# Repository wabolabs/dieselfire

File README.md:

# DieselFire

> **⚠ ALPHA QUALITY — NOT TESTED ON HARDWARE**
>
> This project is in early development. The firmware has **not** been tested on
> physical ESP32-S3 hardware. All protocol simulation and UI development has
> been done via the **PC simulator**. There are likely bugs, edge cases, and
> incomplete drivers. Use at your own risk. Hardware bringup is in progress.

A modernized open-source controller for generic Chinese diesel heaters, forked from [Afterburner](https://gitlab.com/mrjones.id.au/bluetoothheater) by Ray Jones.

## Overview

DieselFire is a complete redesign of the Afterburner project, updated with modern hardware while preserving the core functionality that made Afterburner popular:

- **Diesel heater control** via the "blue wire" half-duplex serial protocol (25000 baud)
- **WiFi connectivity** for web interface, MQTT, and OTA updates
- **Bluetooth Low Energy** for mobile app control
- **Environmental monitoring** with temperature, humidity, pressure, and CO detection
- **Color touchscreen UI** with LVGL graphics
- **Programmable timers** (14 channels)
- **Fuel gauge** and hour meter
- **Smart error detection**

## Online Simulator

Try the DieselFire UI in your browser without any hardware:
**[dieselfire.wabo.cc](https://dieselfire.wabo.cc)**

Runs as a WebAssembly build of the native PC simulator. Includes the full
touchscreen interface, Blue Wire protocol simulation, and a diesel heater
emulator for testing all states and fault conditions.

## Hardware

| Component | Specification |
|---|---|
| **MCU** | ESP32-S3-WROOM-1-N8R8 (8MB flash, 8MB PSRAM) |
| **Display** | 2.8" 320×240 ILI9341 TFT with capacitive touch (GT911) |
| **Ambient Sensor** | BME280 (temperature, humidity, pressure/altitude) |
| **CO Sensor** | MQ-7 carbon monoxide (external module) |
| **RTC** | DS3231 with CR2032 battery backup |
| **External Temp** | DS18B20 waterproof probe (optional) |
| **Power** | 12V DC input (heater system voltage) |
| **Connectivity** | USB-C (programming/debug), WiFi, BLE 5 |
| **Expansion** | 2× 2×10 GPIO headers |

## License

DieselFire is released under the **GNU General Public License v3.0**.

This project is a **fork** of [Afterburner](https://gitlab.com/mrjones.id.au/bluetoothheater) by Ray Jones (Copyright 2018-2020). The original Afterburner code was used as the foundation and has been substantially modified and modernized. All original Afterburner code remains under GPLv3 as per the original license.

See [LICENSE](LICENSE) for the full license text.

## Quick Start

1. **Hardware**: Order PCB from JLCPCB/PCBWay using Gerber files in `gerber/`
2. **Firmware**: Install PlatformIO, then run `pio run` to build
3. **Flash**: Connect via USB-C and run `pio run --target upload`
4. **Configure**: Connect to the AP "DieselFire" (password: thereisnospoon) or connect to existing WiFi

## Project Structure

```
DieselFire/
├── boards/                  # PlatformIO board definitions
├── docs/
│   ├── design/              # Design documents and specifications
│   ├── firmware/            # Firmware documentation
│   └── hardware/            # Hardware documentation
├── gerber/                  # PCB fabrication files
├── kicad/
│   ├── schematic/           # KiCad schematic files
│   ├── pcb/                 # KiCad PCB layout files
│   ├── footprints/          # Custom KiCad footprints
│   └── libraries/           # KiCad symbol libraries
├── lib/                     # PlatformIO libraries (vendored)
├── src/
│   ├── cfg/                 # Configuration headers
│   ├── Display/             # LVGL display driver and screens
│   ├── Protocol/            # Blue wire protocol handling
│   ├── RTC/                 # Real-time clock and timers
│   ├── Utility/             # Utility classes (sensors, storage, etc.)
│   ├── WiFi/                # WiFi, web server, OTA
│   ├── Bluetooth/           # BLE implementation
│   └── OLED/                # Legacy OLED code (to be removed)
├── platformio.ini           # PlatformIO project configuration
├── README.md
└── LICENSE
```

## Features

### Heater Control
- Power on/off commands
- Temperature setpoint adjustment
- Fuel mixture tuning
- Pump priming
- Thermostat mode (cyclic, stop/start, linear)
- Frost protection mode
- Humidity-based control
- OEM controller co-existence mode

### Connectivity
- **WiFi**: STA mode (connect to existing network) or AP mode (captive portal)
- **BLE 5**: Bluetooth Low Energy for mobile app control
- **MQTT**: Publish heater status and receive commands
- **Web Server**: HTTPS web interface with WebSocket JSON streaming
- **OTA**: Over-the-air firmware updates

### Sensors
- **BME280**: Ambient temperature, humidity, pressure (altitude)
- **MQ-7**: Carbon monoxide detection (external module)
- **DS18B20**: External waterproof temperature probe (optional)
- **SCD41**: CO2 sensing (optional, not on default board)

### User Interface
- **2.8" Color Touchscreen**: 320×240 ILI9341 with capacitive touch
- **LVGL Graphics**: Hardware-accelerated UI with PSRAM buffer
- **Menu System**: Hierarchical menus for all settings
- **Timer Chart**: Visual overview of 14 programmable timers
- **Status Display**: Real-time heater status, sensor readings, alerts

### Safety
- **CO Detection**: MQ-7 sensor with alarm LED
- **Low Voltage Cutout**: Auto-shutdown when battery voltage is too low
- **Error Detection**: Smart monitoring of heater state transitions
- **Watchdog**: Hardware and software watchdog for reliability

## Pinout

### ESP32-S3 GPIO Mapping

| Peripheral | GPIO | Interface | Notes |
|---|---|---|---|
| **Native USB** | IO19 (DP) / IO20 (DN) | USB 1.1 | USB-C, programming + debug |
| **SPI Display** | IO18 (MOSI) / IO17 (SCK) / IO16 (MISO) | SPI (HSPI) | ILI9341, 320×240 |
| **Display CS** | IO15 | GPIO | TFT chip select |
| **Display DC** | IO14 | GPIO | TFT data/command |
| **Display RST** | IO13 | GPIO | TFT reset |
| **Display BL** | IO12 | GPIO/PWM | TFT backlight |
| **Touch I2C** | IO21 (SDA) / IO10 (SCL) | I2C (GPIO) | GT911 capacitive touch |
| **Touch INT** | IO9 | GPIO | Touch interrupt |
| **Touch RST** | IO8 | GPIO | Touch reset |
| **Blue Wire UART** | IO43 (TX) / IO44 (RX) | UART0 @ 25kbps | Heater communication |
| **Tx Gate** | IO47 | GPIO | 74LCX125 control |
| **BME280 I2C** | IO21 (SDA) / IO22 (SCL) | I2C (VSPI) | Temp/RH/Pressure |
| **DS3231 I2C** | IO21 (SDA) / IO22 (SCL) | I2C (VSPI) | RTC |
| **DS18B20** | IO45 | OneWire | External temp probe |
| **MQ-7 AOUT** | IO4 | ADC1 (12-bit) | CO analog reading |
| **MQ-7 DOUT** | IO5 | GPIO input | CO digital alert |
| **Status LED** | IO48 | GPIO | Green, active-low |
| **CO Alarm LED** | IO44 | GPIO | Red, active-low |
| **Power Button** | IO0 | GPIO (input) | With pull-up |
| **Reset Button** | IO5 | GPIO | Standard boot button |

### Expansion Headers

**H1 (2×10):** GPIO33, GPIO34, GPIO35, GPIO36, GPIO37, GPIO38, GPIO39, GPIO40, 3.3V, GND, GND
**H2 (2×10):** GPIO41, GPIO42, GPIO43, GPIO44, GPIO45, GPIO46, GPIO47, GPIO48, 3.3V, GND, GND

### Connectors

| Connector | Type | Purpose |
|---|---|---|
| J1 | USB-C | Programming, debug, power |
| J2 | 2-pin terminal block (3.81mm) | 12V power input |
| J3 | 3-pin JST-XH (2.5mm) | Blue wire to heater |
| J4 | 3-pin JST-XH (2.5mm) | DS18B20 external temp sensor |
| J5 | 4-pin JST-XH (2.5mm) | MQ-7 CO sensor |
| H1, H2 | 2×10 header (2.54mm) | Expansion GPIO |

## Building

### Prerequisites

- [PlatformIO](https://platformio.org/) (latest version)
- ESP32-S3 compatible board (DieselFire PCB)
- USB-C cable

### Build Commands

```bash
# Install PlatformIO
pip install platformio

# Clone the repository
git clone https://github.com/wabolabs/DieselFire.git
cd DieselFire

# Build firmware
pio run

# Upload to board
pio run --target upload

# Monitor serial output
pio device monitor --baud 115200
```

### Board Definition

The DieselFire board is defined in `boards/dieselfire.json`. To use it:

```bash
pio run -e dieselfire
```

## Configuration

### WiFi Setup

On first boot, the device creates an access point:
- **SSID**: DieselFire
- **Password**: thereisnospoon

Connect to this AP and open a browser to `192.168.4.1` to configure WiFi.

### MQTT Setup

Configure MQTT settings in the web interface or via the debug console:
- Server address
- Port (1883 for MQTT, 8883 for MQTT over TLS)
- Client ID
- Username/Password (if required)
- Topic prefix

### Sensor Calibration

**MQ-7 CO Sensor:**
1. Power on the device in clean air (outdoors)
2. Wait 48-72 hours for the sensor to stabilize
3. Use the web interface to run calibration
4. The R0 value is stored in non-volatile memory

**DS18B20 Temperature Probe:**
1. Connect the probe to J4
2. The probe will be auto-detected on boot
3. Set offset in settings if needed

## Hardware Design

### PCB Specifications

- **Size**: 80mm × 60mm
- **Layers**: 2-layer
- **Trace width**: 0.2mm signal, 0.5mm power, 1mm 12V
- **Via size**: 0.3mm hole / 0.6mm pad
- **Clearance**: 0.15mm minimum

### BOM

| Reference | Part | Package | Qty | Est. Cost |
|---|---|---|---|---|
| U1 | ESP32-S3-WROOM-1-N8R8 | QFN-44 module | 1 | ~$4.00 |
| U2 | 2.8" ILI9341 TFT + FPC | FPC connector | 1 | ~$3.50 |
| U3 | GT911 | QFN-24 4×4 | 1 | ~$0.80 |
| U4 | BME280 | QFN-8 2×2 | 1 | ~$1.50 |
| U5 | MQ-7 | JST-XH 4-pin | 1 | ~$2.00 |
| U6 | DS18B20 | JST-XH 3-pin | 1 | ~$1.50 |
| U7 | DS3231 | SOIC-16 | 1 | ~$2.00 |
| U8 | 74LCX125 | SOIC-14 | 1 | ~$0.30 |
| U9×2 | BSS138 | SOT-23 | 2 | ~$0.10 |
| U10 | MP2451 | SOT-23-6 | 1 | ~$0.50 |
| U11 | AP2112 | SOT-89-3 | 1 | ~$0.20 |
| J1 | USB-C-S6 | SMD | 1 | ~$0.30 |
| J2 | Terminal Block 2×3.81 | TB | 1 | ~$0.20 |
| J3-J5 | JST-XH connectors | 2.5mm | 3 | ~$0.50 |
| BAT1 | CR2032 Holder | — | 1 | ~$0.50 |
| H1,H2 | 2×10 Header | 2.54mm | 2 | ~$0.20 |
| D1,D2 | LED 0603 | 0603 | 2 | ~$0.05 |
| SW1,SW2 | Tactile 6×6 | 6×6mm | 2 | ~$0.10 |
| Various | Resistors/Caps | 0402/0603 | ~20 | ~$1.00 |
| **Total BOM** | | | | **~$19.00** |

**PCB fabrication:** ~$5-10 for 5 boards (JLCPCB/PCBWay, 2-layer, 80×60mm)

## Firmware Development

### Architecture

The firmware follows a modular architecture:

```
┌─────────────────────────────────────────────────────────────┐
│                     DieselFire                                │
│                                                              │
│  ┌─────────────┐  ┌──────────────┐  ┌──────────────────┐   │
│  │  Display    │  │   UI Layer   │  │  Settings/Config │   │
│  │  (LVGL)     │  │  (Screens)   │  │  (NVS Storage)   │   │
│  └─────────────┘  └──────────────┘  └──────────────────┘   │
│                                                              │
│  ┌─────────────┐  ┌──────────────┐  ┌──────────────────┐   │
│  │  Protocol   │  │  Blue Wire   │  │  Sensor Layer    │   │
│  │  Handling   │  │  State Machine│ │  (BME280, MQ-7)  │   │
│  └─────────────┘  └──────────────┘  └──────────────────┘   │
│                                                              │
│  ┌─────────────┐  ┌──────────────┐  ┌──────────────────┐   │
│  │  WiFi/HTTP  │  │  BLE/Bluetooth│ │  MQTT/OTA        │   │
│  └─────────────┘  └──────────────┘  └──────────────────┘   │
│                                                              │
│  ┌──────────────────────────────────────────────────────┐   │
│  │                    ESP32-S3 Hardware                  │   │
│  └──────────────────────────────────────────────────────┘   │
└─────────────────────────────────────────────────────────────┘
```

### Key Modules

| Module | Description | Location |
|---|---|---|
| **Display** | LVGL integration, ILI9341 driver, GT911 touch | `src/Display/` |
| **Protocol** | Blue wire protocol, state machine, Tx management | `src/Protocol/` |
| **RTC** | Real-time clock, timers, timer manager | `src/RTC/` |
| **Utility** | Sensors, NV storage, JSON, GPIO helpers | `src/Utility/` |
| **WiFi** | WiFiManager, web server, OTA, MQTT | `src/WiFi/` |
| **Bluetooth** | BLE implementation | `src/Bluetooth/` |
| **OLED** | Legacy OLED screens (to be replaced by LVGL) | `src/OLED/` |

### Development Workflow

1. **Create a feature branch**
   ```bash
   git checkout -b feature/new-screen
   ```

2. **Make changes**
   - Add/modify code in `src/`
   - Update documentation in `docs/`

3. **Build and test**
   ```bash
   pio run
   pio run --target upload
   pio device monitor --baud 115200
   ```

4. **Commit and push**
   ```bash
   git add .
   git commit -m "Add new screen for timer overview"
   git push origin feature/new-screen
   ```

5. **Create a pull request**

## Troubleshooting

### Board Won't Flash

- Check USB-C cable (must be data-capable, not charge-only)
- Hold BOOT button while pressing RESET
- Check COM port in `platformio.ini`

### Display Not Working

- Verify FPC connector is seated correctly
- Check SPI pin connections
- Verify PSRAM is detected (check serial output)

### BME280 Not Detected

- Check I2C address (0x76 or 0x77)
- Verify pull-up resistors (4.7kΩ on SDA/SCL)
- Run I2C scanner from debug console

### MQ-7 Readings Unstable

- Ensure 48-72 hour warmup period
- Run calibration in clean air
- Check voltage divider (10kΩ + 10kΩ)
- Verify ADC pin (IO4) is correct

### Blue Wire Communication Issues

- Verify level shifter connections (BSS138)
- Check Tx gate control (IO47)
- Verify UART0 pins (IO43/IO44)
- Check heater blue wire is connected correctly

## Contributing

Contributions are welcome! Please:

1. Fork the repository
2. Create a feature branch
3. Make your changes
4. Submit a pull request

Please ensure your code follows the existing style and includes appropriate documentation.

## Acknowledgments

DieselFire is a fork of [Afterburner](https://gitlab.com/mrjones.id.au/bluetoothheater) by Ray Jones. The original Afterburner project was a groundbreaking open-source controller for Chinese diesel heaters, and this project builds upon that foundation.

Special thanks to:
- Ray Jones (Afterburner original author)
- James Clark (Afterburner co-author)
- The Afterburner community on GitLab
- The ESP32 and LVGL communities

## Disclaimer

DieselFire is provided "as is" without warranty of any kind. The authors are not responsible for any damage caused by the use of this software or hardware. Diesel heaters produce carbon monoxide and other hazardous gases. Always ensure proper ventilation and installation.

Use at your own risk.

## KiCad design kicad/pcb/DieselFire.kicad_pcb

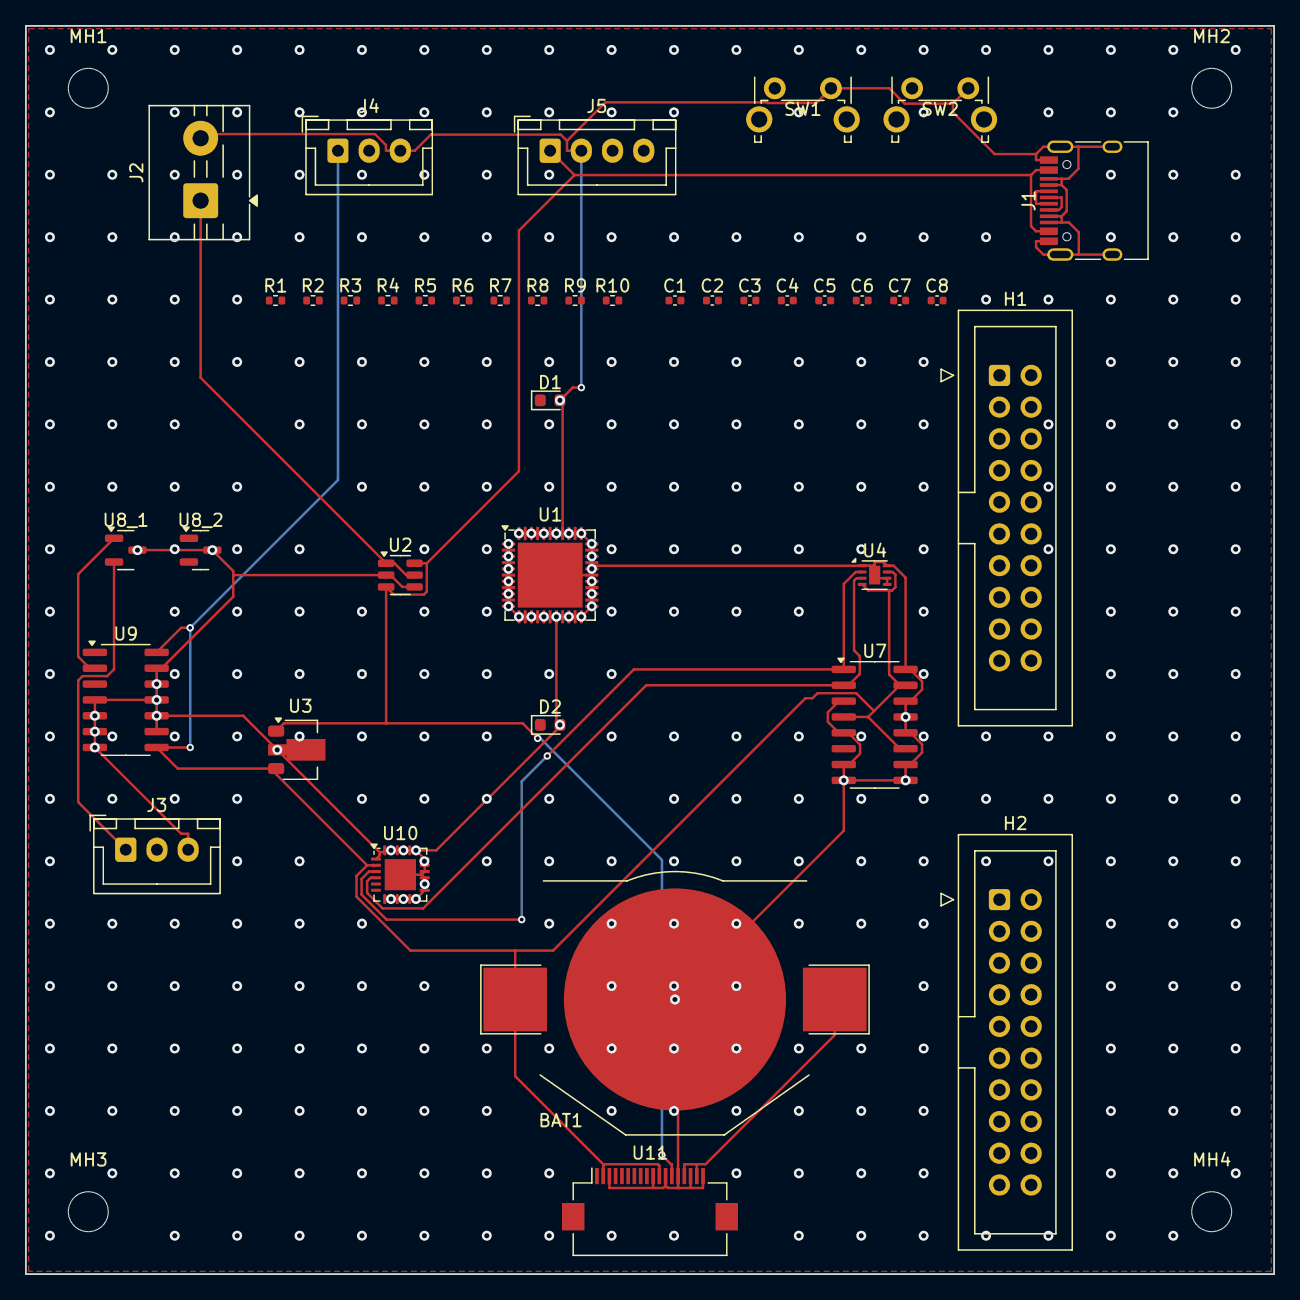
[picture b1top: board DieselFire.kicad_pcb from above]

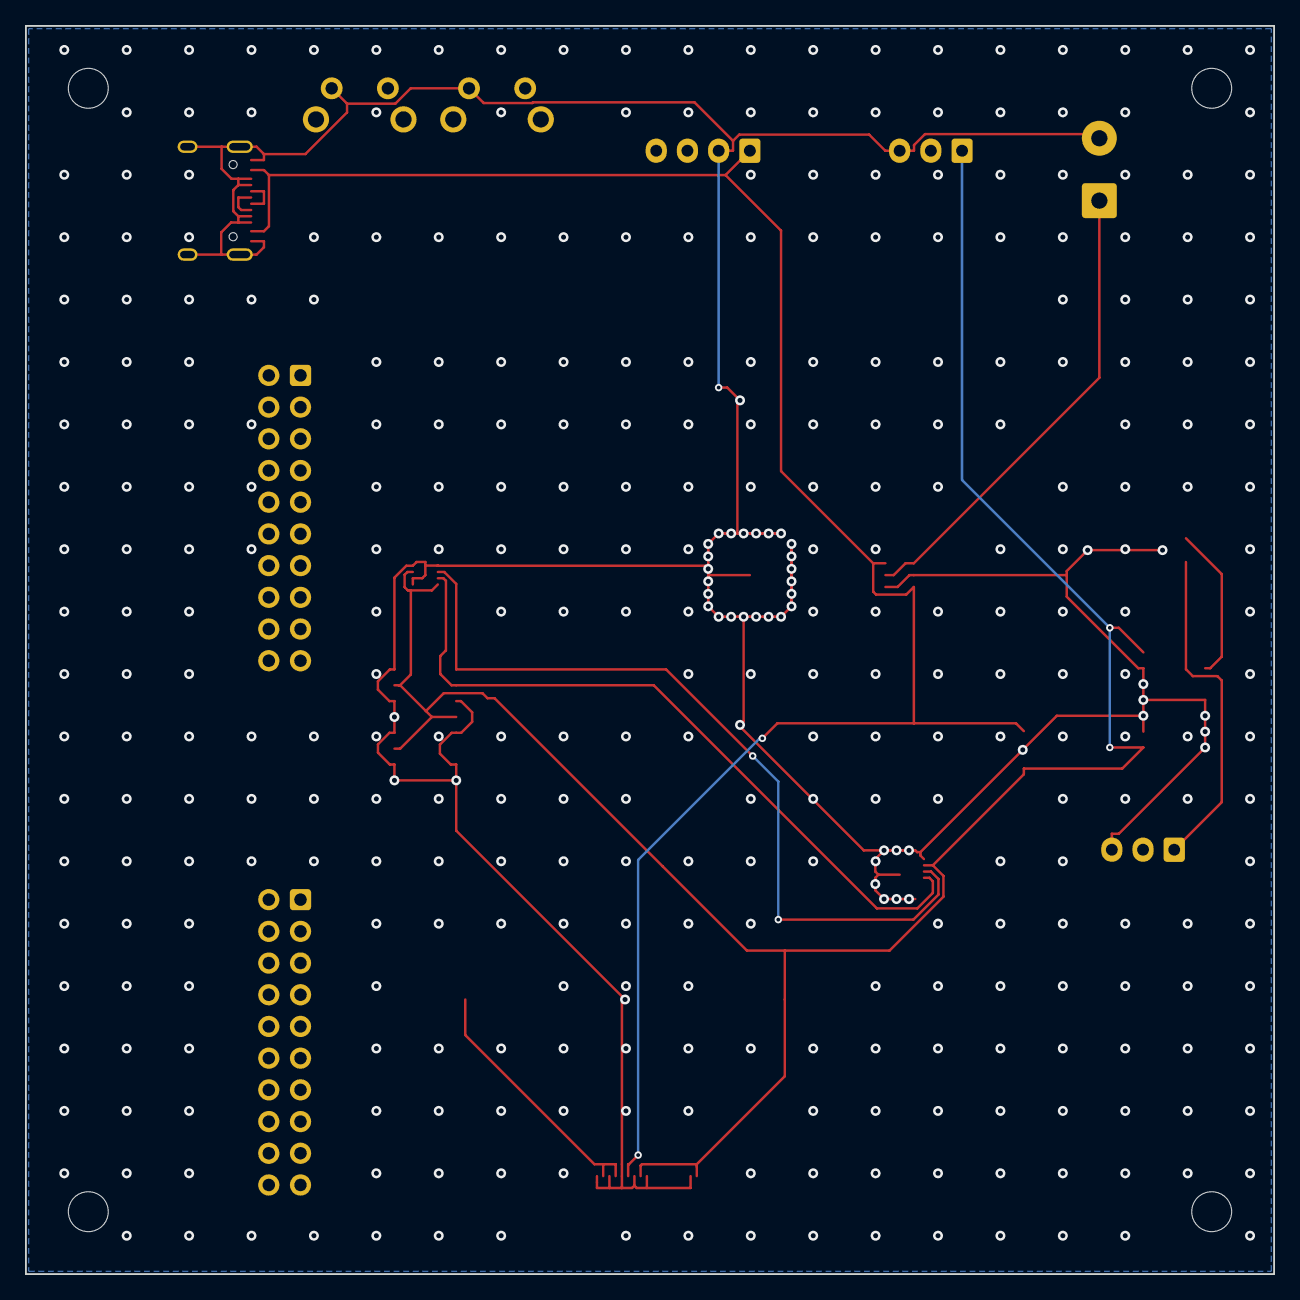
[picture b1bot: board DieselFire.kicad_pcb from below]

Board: 2 copper layers, 100.0 x 100.0 mm, 44 parts (4 on the bottom side), 10 nets.

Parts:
BAT1: BatteryHolder_Keystone_3002_1x2032
C1, C2, C3, C4, C5, C6, C7, C8: C_0402_1005Metric
D1, D2: LED_0603_1608Metric
H1, H2: IDC-Header_2x10_P2.54mm_Vertical
J1: USB_C_Receptacle_HRO_TYPE-C-31-M-12
J2: TerminalBlock_MaiXu_MX126-5.0-02P_1x02_P5.00mm
J3, J4: JST_XH_B3B-XH-A_1x03_P2.50mm_Vertical
J5: JST_XH_B4B-XH-A_1x04_P2.50mm_Vertical
MH1, MH2, MH3, MH4: MountingHole_3.2mm_M3
R1, R2, R3, R4, R5, R6, R7, R8, R9, R10: R_0402_1005Metric
SW1, SW2: SW_Tactile_SPST_Angled_PTS645Vx39-2LFS
U1: QFN-44-1EP_7x7mm_P0.5mm_EP5.2x5.2mm
U2: SOT-23-6
U3: SOT-89-3
U4: DFN-8-1EP_2x2mm_P0.5mm_EP0.9x1.5mm
U7: SOIC-16_3.9x9.9mm_P1.27mm
U8_1, U8_2: SOT-23
U9: SOIC-14_3.9x8.7mm_P1.27mm
U10: QFN-24-1EP_4x4mm_P0.5mm_EP2.5x2.5mm
U11: Hirose_FH12-18S-0.5SH_1x18-1MP_P0.50mm_Horizontal

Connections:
3V3: BAT1.1, J4.1, U3.3, U4.4, U4.7, U7.4, U7.11, U7.15, U9.8, U9.14, U10.2, U11.2, U11.11, U11.15, U11.17
5V: J1.A4, J1.A9, J1.B4, J1.B9, J5.1, U2.3, U2.6, U3.1, U11.13
12V: J2.1, U2.1, U2.5
BLUE_TX_H: J3.1, U8_1.2
BLUE_TX_OUT: U8_1.1, U9.2
GND: BAT1.2, D1.2, D2.2, J1.A1, J1.A5, J1.A8, J1.A12, J1.B1, J1.B5, J1.B8, J1.B12, J1.S1, J2.2, J3.3, J4.3, J5.2, SW1.2, SW2.2, U1.1, U1.2, U1.3, U1.4, U1.5, U1.6, U1.7, U1.8, U1.9, U1.10, U1.11, U1.12, U1.13, U1.14, U1.15, U1.16, U1.17, U1.18, U1.19, U1.20, U1.21, U1.22, U1.23, U1.24, U1.25, U1.26, U1.27, U1.28, U1.29, U1.30, U1.31, U1.32, U1.33, U1.34, U1.35, U1.36, U1.37, U1.38, U1.39, U1.40, U1.41, U1.42, U1.43, U1.44, U1.45, U2.2, U2.4, U3.2, U4.1, U4.5, U4.6, U4.8, U4.9, U7.3, U7.5, U7.7, U7.8, U7.9, U7.10, U7.12, U7.13, U7.14, U7.16, U8_1.3, U8_2.3, U9.4, U9.5, U9.6, U9.7, U9.9, U9.10, U9.11, U9.12, U9.13, U10.1, U10.7, U10.8, U10.9, U10.10, U10.11, U10.12, U10.13, U10.14, U10.15, U10.16, U10.17, U10.18, U10.19, U10.20, U10.21, U10.22, U10.23, U10.24, U10.25, U11.3, U11.10, U11.12, U11.14, U11.16, U11.18
I2C_SCL: U4.3, U7.2, U10.4
I2C_SDA: U4.2, U7.1, U10.3
USB_D+: J1.A6, J1.B6
USB_D-: J1.A7, J1.B7

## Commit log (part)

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2026-05-30 Initial commit: DieselFire S3 - ESP32-S3 diesel heater controller
    - KiCad 9.0 PCB project (80x60mm, 2-layer)
    - Schematic with ESP32-S3, power chain, sensors, displays
    - PCB layout with zones, vias, and tracks
    - Custom symbol and footprint libraries
    - ESP32 firmware (PlatformIO/Arduino)
    - Documentation and design files
2026-05-30 docs: Add T-Deck integration plan for DieselFire S3
    - Mechanical stackup with T-Deck and DieselFire S3
    - Inter-board communication via I2C + UART
    - Case design specifications (3D printable)
    - Assembly instructions and wiring diagram
    - Firmware integration approach
2026-05-30 docs: Add PCB layout status and completion guide
    - Document current PCB state (zones, vias, test points)
    - Provide component placement guide with positions
    - Instructions for completing layout in KiCad GUI
    - DRC and fabrication steps
2026-06-02 Fix PCB DRC violations: increase board to 100mm, remove display mount holes, re-space components
2026-06-02 firmware: establish DieselFire foundation (ESP32-S3, LVGL-ready, new pins)
    - Create boards/dieselfire.json (ESP32-S3, 8MB flash + PSRAM)
    - Create 8MB_partition.csv (larger app slots + 2MB SPIFFS)
    - Rewrite platformio.ini: dieselfire target with PSRAM + lib_deps,
    keep esp32dev target for legacy OLED hardware
    - Rewrite src/cfg/pins.h for new PCB: ILI9341 SPI display (IO16-18),
    GT911 touch I2C (IO10/21), Blue Wire UART (IO43/44), BME280+DS3231
2026-06-03 display: implement LVGL subsystem with LovyanGFX (ILI9341 + GT911)
    - Replace TFT_eSPI with LovyanGFX v1.1.6 (ESP32-S3 optimized, DMA support)
    - Create ILI9341Driver: LovyanGFX panel, SPI bus, PWM backlight, GT911 touch config
    - Create LVGLDisplay: LVGL 9.5 bindings with PSRAM buffers and flush/touch callbacks
    - Remove custom GT911Touch driver (LovyanGFX has native GT911 support)
    - Wire display.init() in main.cpp setup(), taskHandler() in loop()
    - Delete User_Setup.h (no longer needed with LovyanGFX)
2026-06-03 screens: Phase 1 - DieselScreen base + MainStatusScreen with LVGL
    - Add DieselScreen base class: dark/amber theme, header bar (clock, BT,
    WiFi, battery, heater state icons), label/bar/led/nav helpers
    - Add MainStatusScreen: 4-tab tabview (Live Telemetry, Big Temp,
    Clock, Fuel/Priming) with 200ms timer-based updates
    - Enable LVGL Montserrat fonts 8-48 in lv_conf.h
    - Update LVGLDisplay to init theme and load MainStatusScreen
2026-06-03 screens: Phase 2 - settings navigation + Thermostat/Frost/Humidity/Timeouts
    - Add SettingsMenuScreen: list-based navigation hub for config screens
    - Add ThermostatScreen: dropdown for method (Standard/Deadband/Linear Hz/
    Ext Contact/Stop-Start), sliders for window size and cyclic temps
    - Add FrostScreen: sliders for auto-on temperature and auto-off rise
    - Add HumidityScreen: slider for BME280 humidity trigger threshold
    - Add TimeoutsScreen: sliders for display dim timeout and menu timeout
2026-06-03 simulator: fix blank screen and 100% CPU
    - Change LV_DISPLAY_RENDER_MODE_PARTIAL → DIRECT (full frame render)
    - Replace rectangle-copy flush with full memcpy (no byte swapping needed,
    LVGL BGRA == SDL ARGB8888 on little-endian)
    - Add lv_refr_now(display) after screen load (force initial render)
    - Fix timing: remove 5ms threshold, always call lv_tick_inc with delta
    - Cap frame rate at ~60fps (SDL_Delay(16 - elapsed))
2026-06-03 simulator: add test pattern, debug logging, fix LVGL display setup
    - Show color gradient test pattern before LVGL init to verify SDL works
    - Set lv_display_set_default() to activate the display
    - Change to LV_DISPLAY_RENDER_MODE_FULL for simpler buffer handling
    - Use sizeof(lv_color_t) for buffer size instead of hardcoded 4
    - Add flush count and delta logging every 2 seconds
    - Print flush count before/after lv_refr_now for diagnostics
2026-06-03 simulator: fix lv_conf.h path (LV_BUILD_CONF_PATH), add diagnostic output
    - Use correct CMake variable LV_BUILD_CONF_PATH (not LV_CONF_PATH)
    so LVGL finds the simulator's lv_conf.h (not the project root's)
    - Add step-by-step diagnostic prints for display creation
    - Fall back to PARTIAL render mode if needed
    - Disable ThorVG to avoid potential init complications
2026-06-03 simulator: add SDL direct draw test after LVGL render
    - Show solid red/blue split screen after LVGL init to verify
    SDL still works after LVGL sets up its buffers
    - Replace complex test screen with simple amber background +
    white labels (minimal LVGL rendering test)
2026-06-03 simulator: fix screen creation - use NULL parent for screen objects
    - DieselScreen constructor was creating screens as children of
    lv_screen_active() instead of as standalone screen objects (NULL parent)
    - This caused LVGL to render the screen background but skip all children
    (tabview, header, labels, etc.) since they were on a non-screen object
    - Fix both simulator/screens/ and src/Display/Screens/ copies
    - Clean up main.cpp: remove all diagnostics, keep DIRECT mode + shared FB
2026-06-03 screens: Phase 4 - WiFi, MQTT, Bluetooth status screens
    - WiFiScreen: shows mode, IP, RSSI, OTA status with 2s timer updates
    - MQTTScreen: shows connection status, QoS, topic prefix
    - BTScreen: shows BLE status, MAC address, type info
    - SettingsMenu: add network screens to top of settings list
    - Fix lv_timer_get_user_data in WiFiScreen lambda
2026-06-03 screens: Phase 5 - Sensor and GPIO screens
    - SensorScreen: live readout of ambient temp, humidity, altitude
    (BME280) and external temp (DS18B20) with 1s timer updates
    - GPIOScreen: live status of GPIO input states, output states,
    and analog value with 500ms updates
    - Mock TempSense.h: sensor stubs returning realistic values
    - Mock DF_GPIO.h: GPIO class stubs for simulator build
2026-06-03 screens: Phase 7 - system utility screens
    - SystemScreen: firmware version, board revision, WiFi/menu mode
    - RebootScreen: countdown display with timer (10-0)
    - PasswordScreen: 4-digit PIN entry with numeric keypad (1688)
    - HourMeterScreen: run/glow/uptime hour display
    - InheritScreen: OEM controller settings import instructions
    - All screens added to SettingsMenu
2026-06-03 fix: settings menu item visibility and layout
    - Set explicit button height (32px) and padding for list items
    - Set label text color to white on both button and child label
    - Remove button borders for cleaner appearance
2026-06-03 fix: replace header icons with proper buttons for reliable click handling
    - Back arrow changed from label to lv_button (36x20px) with "← Back" text
    - Settings gear changed from label to lv_button (36x20px)
    - Both buttons have hover/active state styling
    - Adds createContentArea() helper for scrollable content below header
2026-06-03 fix: clean up sub-screens on navigation to prevent memory exhaustion
    - SettingsMenuScreen now tracks _subScreen and deletes it before opening
    a new one (prevents LVGL memory pool exhaustion after N navigations)
    - Back callback: deletes sub-screen's LVGL object and C++ object after
    restoring the settings menu screen
    - Fix header spacing: increase back arrow and settings gear to 22x22px,
    position at x=4 and x=TFT_WIDTH-24 respectively
2026-06-03 fix: restore header icons, add settings back navigation, scrollable timer
    - Restore BT/WiFi/battery/heater status icons in header bar with
    compact spacing (14px each, right-aligned between clock and gear)
    - Restore updateHeader* methods from no-ops to properly update icons
    - SettingsMenuScreen: remove hideBackButton, add onBack() that creates
    a fresh MainStatusScreen (back arrow returns to main screen)
    - TimerEditScreen: use scrollable content area (createContentArea)
2026-06-03 feat: Home Assistant MQTT autodiscovery + climate integration
    - sMQTTparams: add haDiscovery flag (default on, stored as haDisc in NVS)
    - HADiscovery: publish discovery configs on MQTT connect for 3 entities:
    - Climate entity (off/heat/auto modes, eco/none/boost presets)
    - 8 sensor entities (heat exchanger temp, run state, error, fuel, fan, voltage, pump)
    - 2 binary sensors (running, has_error)
    - Publish HA state topics on each blue wire cycle:
2026-06-03 feat: native Blue Wire protocol simulator with heater emulation
    Architecture:
    BlueWireTask thread (std::thread via FreeRTOS adapter)
    ↔ VirtualSerial (socketpair)
    ↔ HeaterEmulator thread
    New files:
    - simulator/include/FreeRTOS.h — FreeRTOS→C++17 adapter
2026-06-03 feat: re-implement DFWebServer with ESPAsyncWebServer
    Replaces the removed fhessel/esp32_https_server library dependency with
    me-no-dev/ESPAsyncWebServer, which uses the already-vendored AsyncTCP.
    New implementation (src/WiFi/DFWebServer.cpp, ~300 lines vs 1841):
    - AsyncWebServer on port 80 with WebSocket support
    - Routes: / (SPIFFS), /update (OTA upload), /reboot, /formatspiffs,
    /wmconfig, /resetwifi, 404 with SPIFFS listing
2026-06-03 chore: remove generated fota.json, add to gitignore
2026-06-03 feat: MQ-7 CO sensor driver + clean up redundant BME280
    New files:
    - src/Utility/MQCOSensor.h/cpp: MQ-7 CO gas sensor driver
    - ADC1_CHANNEL_3 (GPIO4) 12-bit reading with EMA filter
    - Voltage divider correction (10k+10k = 2:1 ratio)
    - Rs/R0 ratio using sensor circuit model (Vc=5V, Rl=10k)
    - CO concentration via log-log sensitivity curve
2026-06-03 chore: gitignore build directories and test artifacts
2026-06-03 chore: pre-public cleanup — remove artifacts, fix branding, add alpha disclaimer
    Cleanup before making repo public:
    Removed tracked artifacts:
    - Bootload/ (Afterburner firmware binaries, Windows exes, bootloader archives)
    - Arduino/Afterburner/ (old Arduino IDE project)
    - kicad/Afterburner-Modern* (old KiCad project)
    - kicad/fabrication/ (generated PCB outputs: gerbers, CPL, pick-and-place)
2026-06-03 feat: SemVer 0.1.0 — pre-release versioning
    Change firmware version from V3.3 to V0.1.0 (SemVer, pre-1.0.0).
    - FirmwareRevision 33→1, SubRevision 0→0 → getVersionStr() = "V0.1.0"
    - FOTA version code: int((1*0.1 + 0*0.001)*1000) = 100
    - Script docstring updated to show 0.1.0 examples
2026-06-03 fix: WASM build — DebugPort.h needs EMSCRIPTEN guard, WiFi.h duplicate typedef
    - DebugPort.h: TelnetSpy include path now also guarded for __EMSCRIPTEN__
    (previously only __linux__, but Emscripten doesn't define __linux__)
    - WiFi.h mock: removed duplicate typedef int arduino_event_t that conflicted
    with the struct definition on line 44
2026-06-03 fix: WASM deploy — add contents:write permission, explicit git user
2026-06-03 deploy: 5d5ab886740bff90be257121c8dcef84380362f9
2026-06-03 fix: WASM output as index.html (GitHub Pages default) + build fixes
    - CMakeLists.txt: set OUTPUT_NAME to "index" so Emscripten generates
    index.html (GitHub Pages default document)
    - shell.html: change script src from dieselfire-sim.js to index.js
    - workflow: remove shell copy step (handled by CMake now)
    - Remove --shell-file flag (use default Emscripten shell for now)
2026-06-03 fix: Pages deploy — add cname parameter so CNAME isn't wiped
2026-06-03 fix: add .nojekyll to Pages deploy
2026-06-03 fix: switch to native actions/deploy-pages for WASM deployment
    The legacy Pages builder fails on .wasm/.js output. Switch to the native
    GitHub Actions Pages deployment (actions/upload-pages-artifact +
    actions/deploy-pages) which bypasses the legacy builder entirely.
2026-06-04 feat: project landing page at dieselfire.wabo.cc, simulator at /sim/
    Root index.html describes the project, features, and links to GitHub.
    The WASM simulator is served at /sim/index.html.
    Landing page styled in dark theme matching the LVGL UI.
2026-06-04 fix: critical UI gaps — heater ON/OFF, temp control, fuel prime, reboot
    - MainStatusScreen: added START/STOP button on Data tab that calls
    requestOn()/requestOff(). Button switches color orange/red based on
    heater state. Fuel tab: PRIME/STOP toggle + RESET fuel gauge buttons.
    Temp tab: +/- setpoint controls calling CDemandManager::deltaDemand().
    - RebootScreen: now calls ESP.restart() when countdown reaches zero
    (was decrementing past zero forever).
